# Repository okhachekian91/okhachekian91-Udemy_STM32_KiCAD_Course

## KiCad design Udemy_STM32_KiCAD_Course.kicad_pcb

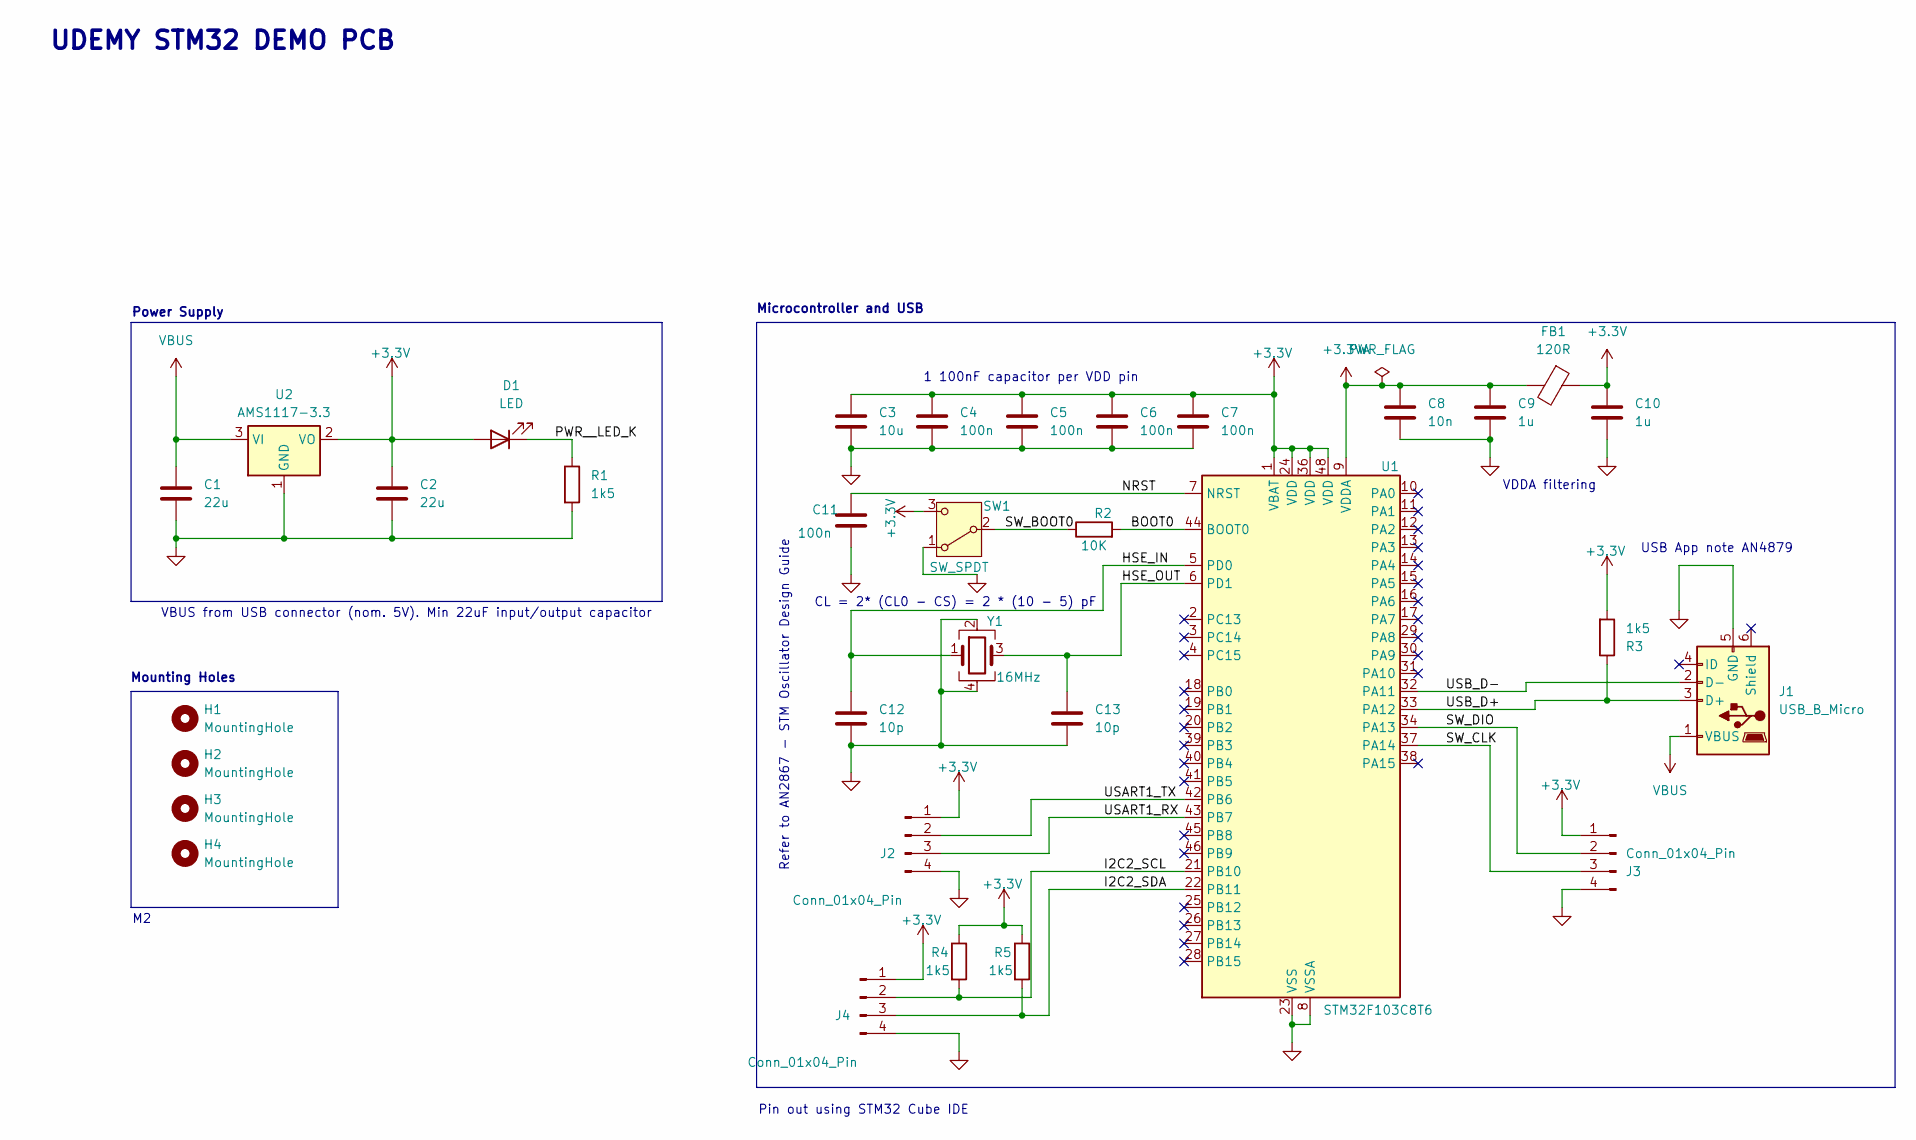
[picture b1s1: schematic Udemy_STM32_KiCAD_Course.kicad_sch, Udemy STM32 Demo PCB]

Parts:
C1, C2: 22u; C_0805_2012Metric
C3: 10u; C_0603_1608Metric
C4, C5, C6, C7, C11: 100n; C_0402_1005Metric
C8: 10n; C_0402_1005Metric
C9, C10: 1u; C_0402_1005Metric
C12, C13: 10p; C_0402_1005Metric
D1: LED; LED_0603_1608Metric
FB1: 120R; L_0603_1608Metric
H1, H2, H3, H4: MountingHole; MountingHole_2.2mm_M2
J1: USB_B_Micro; USB_Micro-B_Wuerth_629105150521
J2, J3, J4: Conn_01x04_Pin; PinHeader_1x04_P2.54mm_Vertical
R1, R3, R4, R5: 1k5; R_0402_1005Metric
R2: 10K; R_0402_1005Metric
SW1: SW_SPDT; SW_SPDT_PCM12
U1: STM32F103C8T6; LQFP-48_7x7mm_P0.5mm
U2: AMS1117-3.3; SOT-223-3_TabPin2
Y1: 16MHz; Crystal_SMD_3225-4Pin_3.2x2.5mm

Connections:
+3.3V: C2.1, C3.1, C4.1, C5.1, C6.1, C7.1, C10.1, D1.2 (A), FB1.1, J2.1, J3.1, J4.1, R3.2, R4.1, R5.1, SW1.3 (C), U1.1 (VBAT), U1.24 (VDD), U1.36 (VDD), U1.48 (VDD), U2.2 (VO)
+3.3VA: C8.1, C9.1, FB1.2, U1.9 (VDDA)
/BOOT0: R2.2, U1.44 (BOOT0)
/HSE_IN: C12.1, U1.5 (PD0), Y1.1
/HSE_OUT: C13.1, U1.6 (PD1), Y1.3
/I2C2_SCL: J4.2, R4.2, U1.21 (PB10)
/I2C2_SDA: J4.3, R5.2, U1.22 (PB11)
/NRST: C11.1, U1.7 (NRST)
/PWR__LED_K: D1.1 (K), R1.1
/SW_BOOT0: R2.1, SW1.2 (B)
/SW_CLK: J3.3, U1.37 (PA14)
/SW_DIO: J3.2, U1.34 (PA13)
/USART1_RX: J2.3, U1.43 (PB7)
/USART1_TX: J2.2, U1.42 (PB6)
/USB_D+: J1.3 (D+), R3.1, U1.33 (PA12)
/USB_D-: J1.2 (D-), U1.32 (PA11)
GND: C1.2, C2.2, C3.2, C4.2, C5.2, C6.2, C7.2, C8.2, C9.2, C10.2, C11.2, C12.2, C13.2, J1.5 (GND), J2.4, J3.4, J4.4, R1.2, SW1.1 (A), U1.8 (VSSA), U1.23 (VSS), U1.35 (VSS), U1.47 (VSS), U2.1 (GND), Y1.2, Y1.4
VBUS: C1.1, J1.1 (VBUS), U2.3 (VI)

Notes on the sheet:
VDDA filtering
Refer to AN2867 - STM Oscillator Design Guide
Power Supply
USB App note AN4879
VBUS from USB connector (nom. 5V). Min 22uF input/output capacitor
1 100nF capacitor per VDD pin
Pin out using STM32 Cube IDE
UDEMY STM32 DEMO PCB
Mounting Holes
Microcontroller and USB
CL = 2* (CL0 - CS) = 2 * (10 - 5) pF

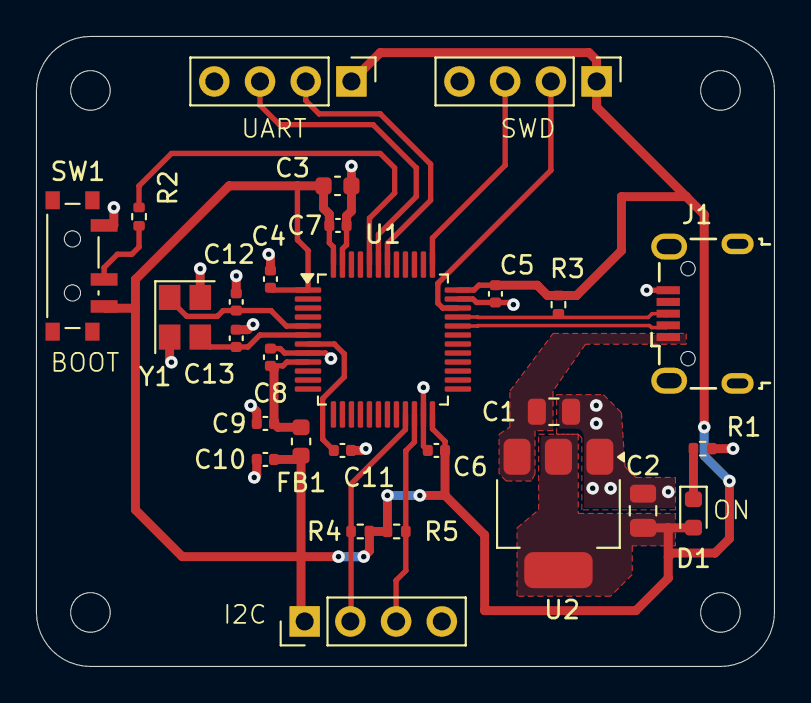
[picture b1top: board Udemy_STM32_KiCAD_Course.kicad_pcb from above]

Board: 2 copper layers, 41.0 x 35.0 mm, 32 parts (0 on the bottom side), 18 nets.

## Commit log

2024-09-15 added voltage regulator
2024-09-22 complete schematic and annotations
2024-09-22 Completed layout and routing
